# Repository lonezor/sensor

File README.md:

# Sensor Projects

**PIR Motion Sensor over Ethernet (Waveshare RP2040 ETH)**

**Indoor Temperature/Humidity Sensor over Ethernet (Waveshare RP2040 ETH)**

**Mobile LoRa Connectivity Monitor (Waveshare RP2040 LoRa HF)**

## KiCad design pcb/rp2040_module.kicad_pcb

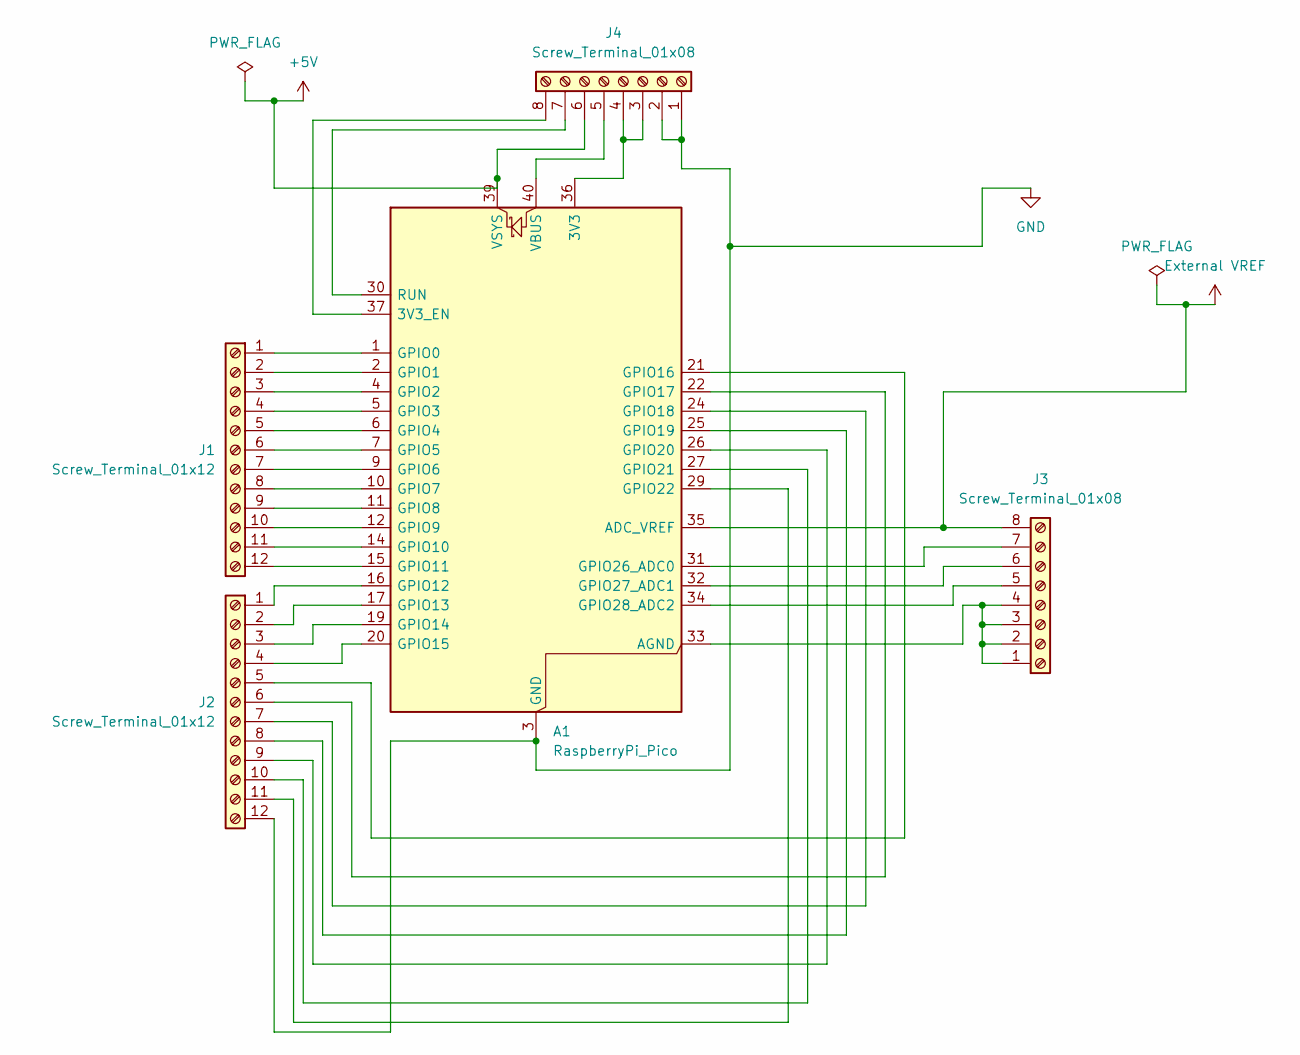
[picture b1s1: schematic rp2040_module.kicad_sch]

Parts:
A1: RaspberryPi_Pico; RaspberryPi_Pico_Common_Unspecified
J1, J2: Screw_Terminal_01x12; TerminalBlock_Phoenix_MKDS-1,5-12_1x12_P5.00mm_Horizontal
J3, J4: Screw_Terminal_01x08; TerminalBlock_Phoenix_MKDS-1,5-8_1x08_P5.00mm_Horizontal

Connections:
+5V: A1.39 (VSYS), J4.6
External VREF: A1.35 (ADC_VREF), J3.8
GND: A1.3 (GND), A1.8 (GND), A1.13 (GND), A1.18 (GND), A1.23 (GND), A1.28 (GND), A1.38 (GND), J2.12, J4.1, J4.2
unnamed: A1.36 (3V3), J4.3, J4.4
unnamed: A1.37 (3V3_EN), J4.8
unnamed: A1.33 (AGND), J3.1, J3.2, J3.3, J3.4
unnamed: A1.1 (GPIO0), J1.1
unnamed: A1.2 (GPIO1), J1.2
unnamed: A1.4 (GPIO2), J1.3
unnamed: A1.5 (GPIO3), J1.4
unnamed: A1.6 (GPIO4), J1.5
unnamed: A1.7 (GPIO5), J1.6
unnamed: A1.9 (GPIO6), J1.7
unnamed: A1.10 (GPIO7), J1.8
unnamed: A1.11 (GPIO8), J1.9
unnamed: A1.12 (GPIO9), J1.10
unnamed: A1.14 (GPIO10), J1.11
unnamed: A1.15 (GPIO11), J1.12
unnamed: A1.16 (GPIO12), J2.1
unnamed: A1.17 (GPIO13), J2.2
unnamed: A1.19 (GPIO14), J2.3
unnamed: A1.20 (GPIO15), J2.4
unnamed: A1.21 (GPIO16), J2.5
unnamed: A1.22 (GPIO17), J2.6
unnamed: A1.24 (GPIO18), J2.7
unnamed: A1.25 (GPIO19), J2.8
unnamed: A1.26 (GPIO20), J2.9
unnamed: A1.27 (GPIO21), J2.10
unnamed: A1.29 (GPIO22), J2.11
unnamed: A1.31 (GPIO26_ADC0), J3.7
unnamed: A1.32 (GPIO27_ADC1), J3.6
unnamed: A1.34 (GPIO28_ADC2), J3.5
unnamed: A1.30 (RUN), J4.7
unnamed: A1.40 (VBUS), J4.5

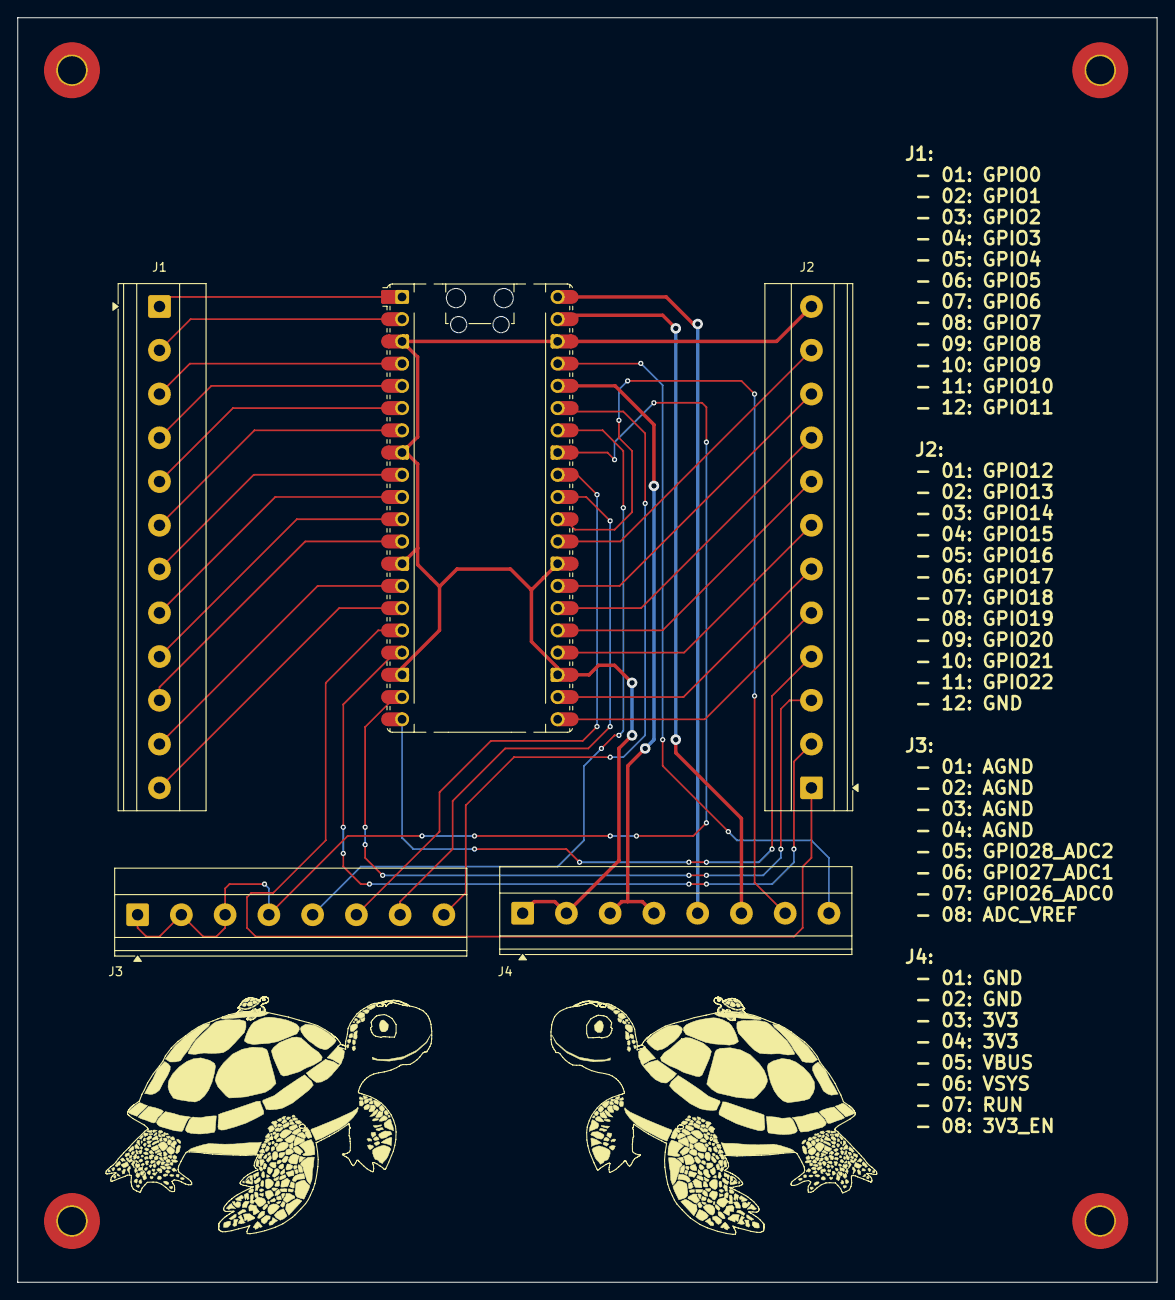
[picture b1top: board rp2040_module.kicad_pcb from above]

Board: 2 copper layers, 130.2 x 144.5 mm, 5 parts (0 on the bottom side), 34 nets.

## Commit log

2026-02-07 PIR Motion Sensor over Ethernet
2026-02-07 Rename pir directory to load in Arduino IDE
2026-02-07 Indoor temperature/humidity sensor over Ethernet
2026-02-27 Mobile LoRa Connectivity Monitor
2026-03-15 Outdoor temp/humidity sensor house via PoE
    OUTDOOR_POE_UNIT_01: internal_temp=26.09 °C, internal_humidity=45.52 , barometric_pressure 1011.96 hPa, outdoor_temp=25.49, outdoor_humidity=42.94
    OUTDOOR_POE_UNIT_01: internal_temp=26.20 °C, internal_humidity=45.17 , barometric_pressure 1012.00 hPa, outdoor_temp=25.36, outdoor_humidity=43.12
    OUTDOOR_POE_UNIT_01: internal_temp=26.32 °C, internal_humidity=44.88 , barometric_pressure 1011.97 hPa, outdoor_temp=25.25, outdoor_humidity=43.28
    OUTDOOR_POE_UNIT_01: internal_temp=26.41 °C, internal_humidity=44.71 , barometric_pressure 1011.96 hPa, outdoor_temp=25.18, outdoor_humidity=43.69
    OUTDOOR_POE_UNIT_01: internal_temp=27.31 °C, internal_humidity=4
2026-04-05 Update indoor temp humidity network setup
2026-04-05 Add server side echart view of temperature readings
2026-06-14 DC power monitor unit
2026-06-14 LoRa radiolib gateway
2026-06-14 LoRa radiolib handheld client
2026-06-14 PoE ground/underground temperature unit
2026-06-14 PoE wind unit
2026-06-14 Add RP2040 PCB for prototyping
